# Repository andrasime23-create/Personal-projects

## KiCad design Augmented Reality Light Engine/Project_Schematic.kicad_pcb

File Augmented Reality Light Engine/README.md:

# Augmented Reality Light Engine

This project involves the complete design and development of an Augmented Reality (AR) Light Engine module. It showcases expertise in high-density electronics, bridging hardware architecture with advanced PCB manufacturing techniques. 

Core Architecture of the project implemented in KiCad: 

-**Powered by a DPLC2020 ASIC (ARM Cortex M3) and a DLPA2020 PMIC** to manage complex power rails.

-**Optical Engine**: Integrates a DLP2020 MEMS projector with OSRAM RGB LEDs to generate high-fidelity AR visuals.

-**Rigid-Flex Technology**: Designed on a 6-layer Rigid-Flex PCB to fit the ergonomic constraints of wearable smart glasses.

-**Signal & Power Integrity**: Implementation of 50Ω single-ended and 100Ω differential pairs for high-speed video data, alongside optimized switching loops for EMC compliance.

-**Thermal Engineering**: Utilizes Copper Inlays (copper coins) and calculated thermal via arrays to dissipate heat from high-power LEDs and the PMIC.

The system also provides manufacturing-ready files, including Extended Gerber, NC Drill, and Pick-and-Place data and detailed thermal resistance calculations and power integrity reports based on IPC-2152 standards, with the possibility of actually sending the prototype to the production line and developing a real functional project.

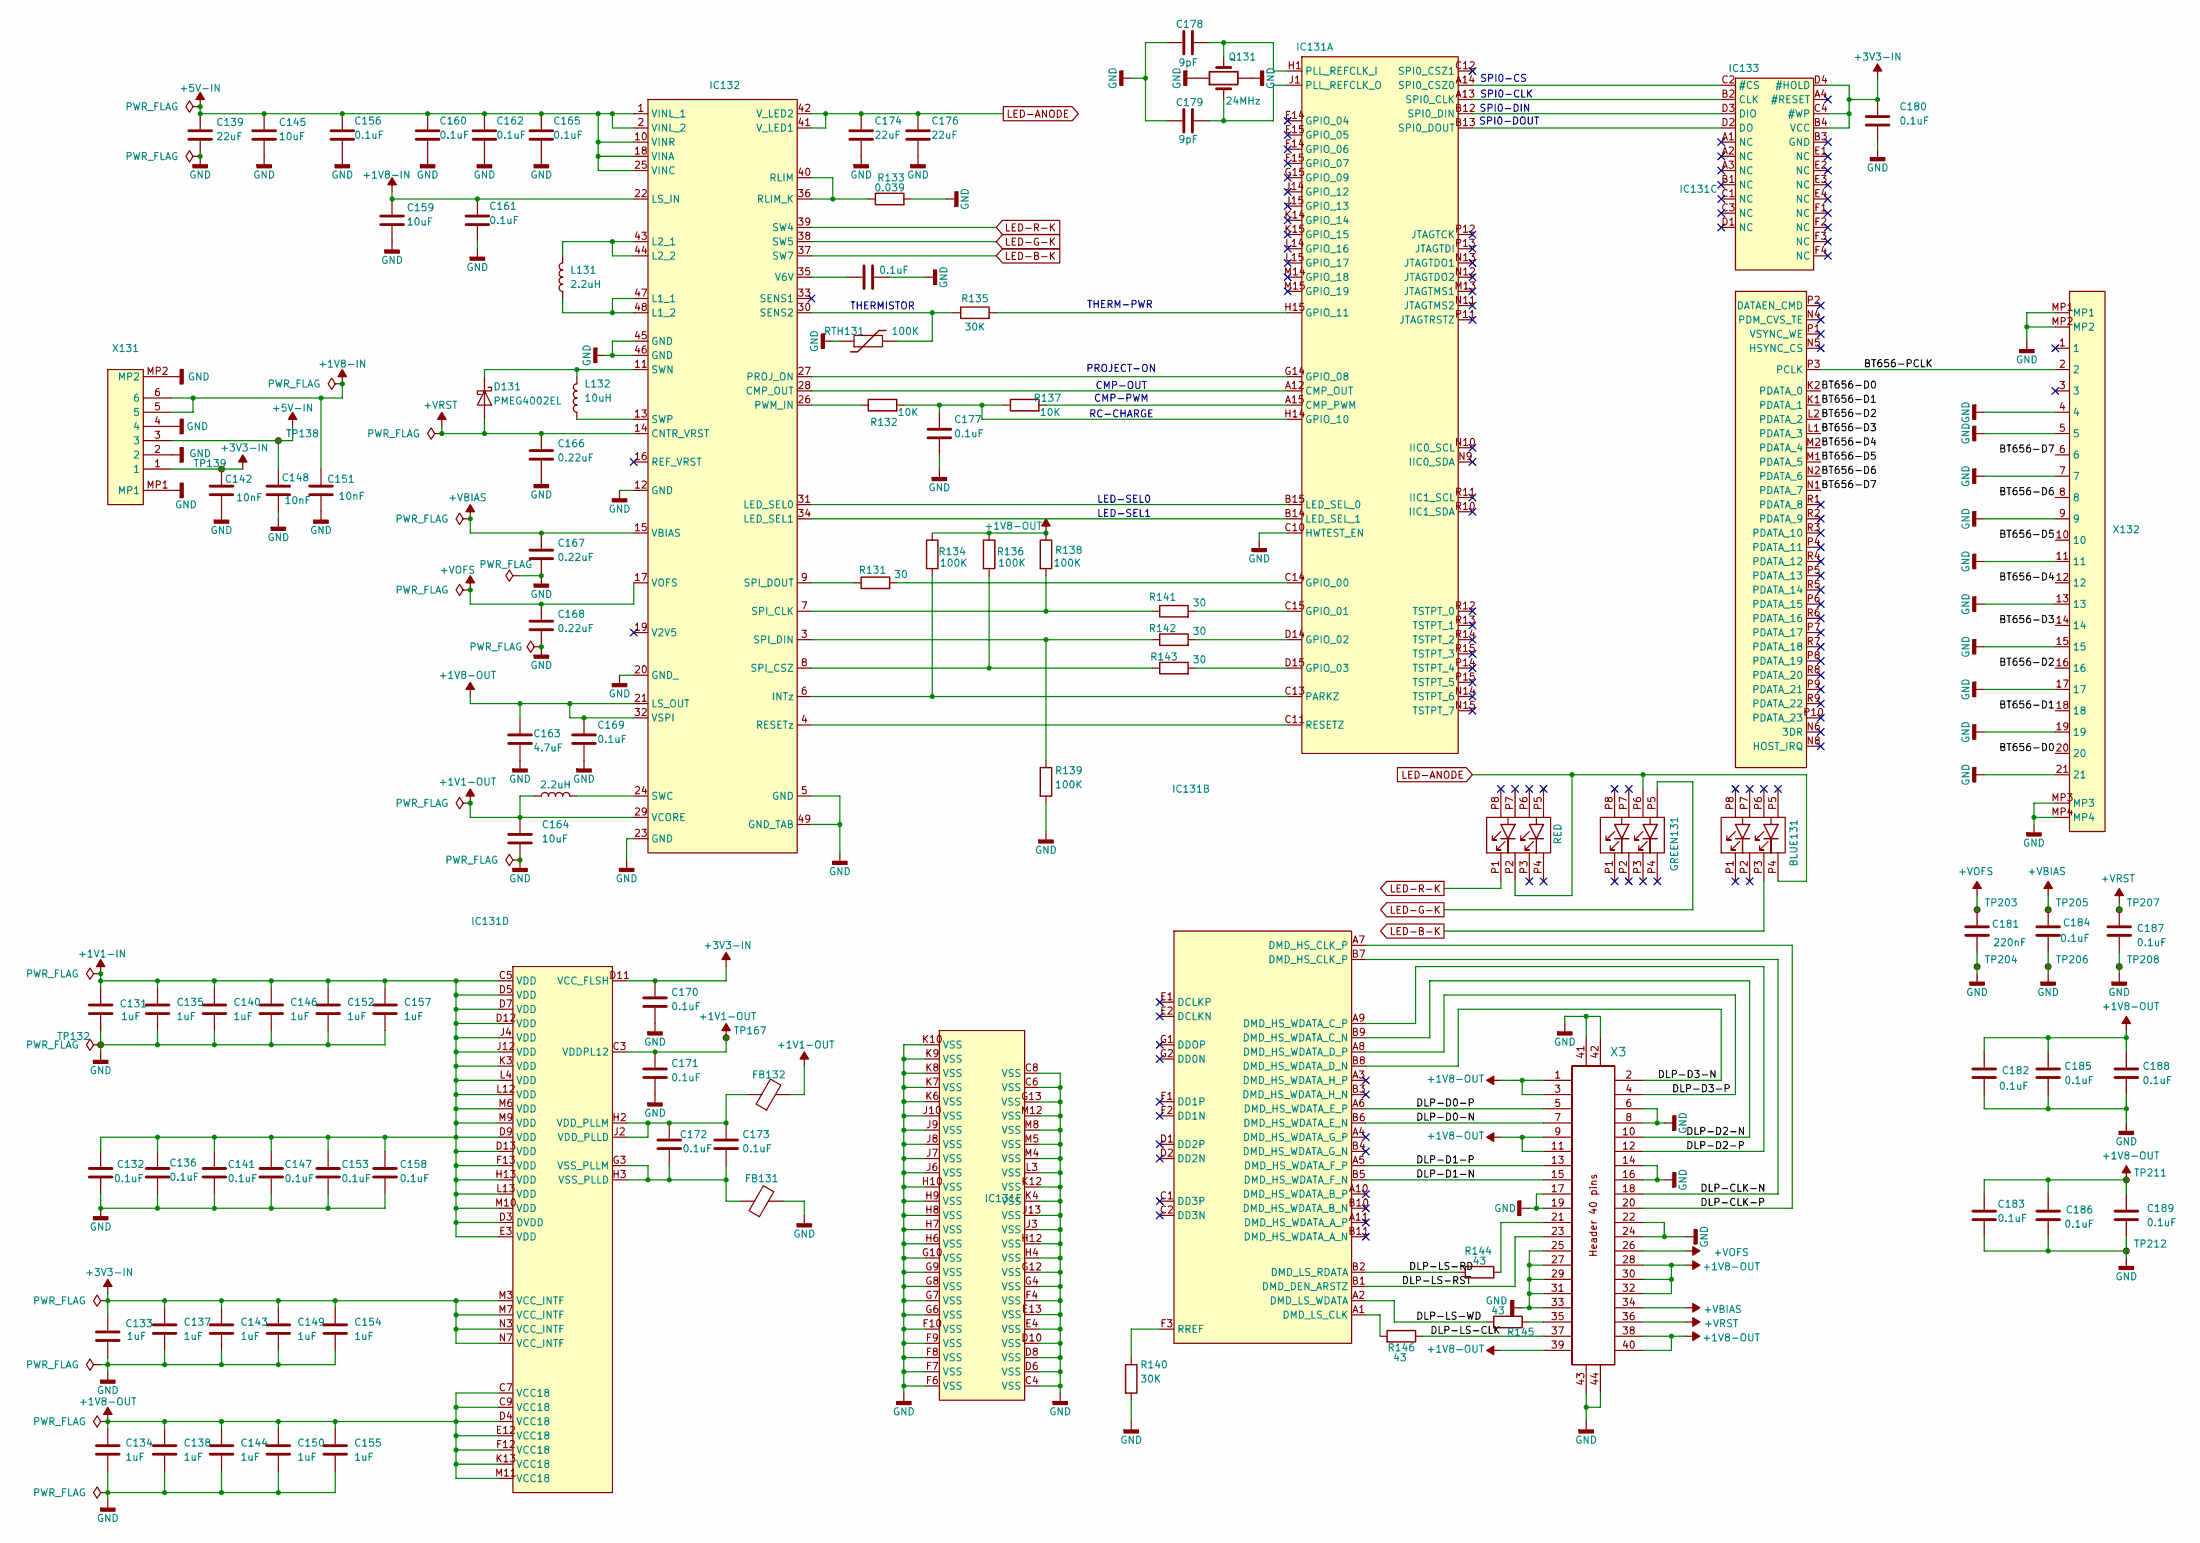
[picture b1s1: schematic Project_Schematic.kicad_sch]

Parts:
BLUE131: LE RTDUW S2WN_OSR
C131, C133, C134, C135, C137, C138, C140, C143, C144, C146, C149, C150, C152, C154, C155, C157: 1uF; C_0402_1005Metric
C132, C136, C141, C147, C153, C156, C158, C160, C161, C162, C165, C169, C170, C171, C172, C173, C175, C177, C180, C182, C183, C184, C185, C186, C187, C188, C189: 0.1uF; C_0402_1005Metric
C139, C174, C176: 22uF; C_0603_1608Metric
C142, C148, C151: 10nF; C_0402_1005Metric
C145, C159, C164: 10uF; C_0603_1608Metric
C163: 4.7uF; C_0603_1608Metric
C166, C167, C168: 0.22uF; C_0402_1005Metric
C178, C179: 9pF; C_0402_1005Metric
C181: 220nF; C_0603_1608Metric
D131: PMEG4002EL; D_SOD-882 (1)
FB131, FB132: FB_0402; L_0402_1005Metric
GREEN131: LE RTDUW S2WN_OSR
IC131: BGA-225_15x15_13.1x13.1mm
IC132: QFN-48_EP_6.8x6.8_Pitch0.4mm
IC133: BGA-24_4x6_6.0x8.0mm
J131: X3; AXT640124
L131: 2.2uH; L_Vishay_IHLP-1616
L132: 10uH; L_0805_2012Metric
LR131: 2.2uH; L_0603_1608Metric
Q131: 24MHz; Oscillator_SMD_Abracon_ASCO-4Pin_1.6x1.2mm
R131, R141, R142, R143: 30; R_0402_1005Metric
R132, R137: 10K; R_0402_1005Metric
R133: 0.039; R_0603_1608Metric
R134, R136, R138, R139: 100K; R_0402_1005Metric
R135, R140: 30K; R_0402_1005Metric
R144, R145, R146: 43; R_0402_1005Metric
RED131: RED; LE RTDUW S2WN_OSR
RTH131: 100K; R_0402_1005Metric
TP132, TP138, TP139, TP167, TP203, TP204, TP205, TP206, TP207, TP208, TP211, TP212: TestPoint_Small; TestPoint_Pad_D1.0mm
X131: CONN06_781715006_MOL
X132: FH6221S025SHW99

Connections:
+1V1-IN: C131.1, C132.1, C135.1, C136.1, C140.1, C141.1, C146.1, C147.1, C152.1, C153.1, C157.1, C158.1, IC131.C5 (VDD), IC131.D3 (DVDD), IC131.D5 (VDD), IC131.D7 (VDD), IC131.D9 (VDD), IC131.D12 (VDD), IC131.D13 (VDD), IC131.E3 (VDD), IC131.F13 (VDD), IC131.H13 (VDD), IC131.J4 (VDD), IC131.J12 (VDD), IC131.K3 (VDD), IC131.L4 (VDD), IC131.L12 (VDD), IC131.L13 (VDD), IC131.M6 (VDD), IC131.M9 (VDD), IC131.M10 (VDD)
+1V1-OUT: C164.1, C171.1, FB132.2, IC131.C3 (VDDPL12), IC132.29 (VCORE), LR131.1, TP167.1
+1V8-IN: C151.1, C159.1, C161.1, IC132.22 (LS_IN), X131.5, X131.6
+1V8-OUT: C134.1, C138.1, C144.1, C150.1, C155.1, C163.1, C169.1, C182.1, C183.1, C185.1, C186.1, C188.1, C189.1, IC131.C7 (VCC18), IC131.C9 (VCC18), IC131.D4 (VCC18), IC131.E12 (VCC18), IC131.F12 (VCC18), IC131.K13 (VCC18), IC131.M11 (VCC18), IC132.21 (LS_OUT), IC132.32 (VSPI), J131.1, J131.3, J131.9, J131.11, J131.28, J131.30, J131.32, J131.38, J131.39, J131.40, R134.1, R136.1, R138.1, TP211.1
+3V3-IN: C133.1, C137.1, C142.1, C143.1, C149.1, C154.1, C170.1, C180.1, IC131.D11 (VCC_FLSH), IC131.M3 (VCC_INTF), IC131.M7 (VCC_INTF), IC131.N3 (VCC_INTF), IC131.N7 (VCC_INTF), IC133.B4 (VCC), IC133.C4 (#WP), IC133.D4 (#HOLD), TP139.1, X131.1
+5V-IN: C139.1, C145.1, C148.1, C156.1, C160.1, C162.1, C165.1, IC132.1 (VINL_1), IC132.2 (VINL_2), IC132.10 (VINR), IC132.18 (VINA), IC132.25 (VINC), TP138.1, X131.3
+VBIAS: C167.1, C184.1, IC132.15 (VBIAS), J131.34, TP205.1
+VOFS: C168.1, C181.1, IC132.17 (VOFS), J131.26, TP203.1
+VRST: C166.1, C187.1, D131.2 (A), IC132.14 (CNTR_VRST), J131.36, TP207.1
/ BT656-D0: IC131.K2 (PDATA_0), X132.20
/ BT656-D1: IC131.K1 (PDATA_1), X132.18
/ BT656-D2: IC131.L2 (PDATA_2), X132.16
/ BT656-D3: IC131.L1 (PDATA_3), X132.14
/ BT656-D4: IC131.M2 (PDATA_4), X132.12
/ BT656-D5: IC131.M1 (PDATA_5), X132.10
/ BT656-D6: IC131.N2 (PDATA_6), X132.8
/ BT656-D7: IC131.N1 (PDATA_7), X132.6
/ BT656-PCLK: IC131.P3 (PCLK), X132.2
/ DLP-D2-N: IC131.B9 (DMD_HS_WDATA_C_N), J131.10
/ DLP-D2-P: IC131.A9 (DMD_HS_WDATA_C_P), J131.12
/DLP-CLK-N: IC131.B7 (DMD_HS_CLK_P), J131.18
/DLP-CLK-P: IC131.A7 (DMD_HS_CLK_P), J131.20
/DLP-D0-N: IC131.B6 (DMD_HS_WDATA_E_N), J131.7
/DLP-D0-P: IC131.A6 (DMD_HS_WDATA_E_P), J131.5
/DLP-D1-N: IC131.B5 (DMD_HS_WDATA_F_N), J131.15
/DLP-D1-P: IC131.A5 (DMD_HS_WDATA_F_P), J131.13
/DLP-D3-N: IC131.B8 (DMD_HS_WDATA_D_N), J131.2
/DLP-D3-P: IC131.A8 (DMD_HS_WDATA_D_P), J131.4
/DLP-LS-CLK: J131.37, R146.2
/DLP-LS-RD: IC131.B2 (DMD_LS_RDATA), R144.1
/DLP-LS-RST: IC131.B1 (DMD_DEN_ARSTZ), J131.23
/DLP-LS-WD: IC131.A2 (DMD_LS_WDATA), R145.1
GND: C131.2, C132.2, C133.2, C134.2, C135.2, C136.2, C137.2, C138.2, C139.2, C140.2, C141.2, C142.2, C143.2, C144.2, C145.2, C146.2, C147.2, C148.2, C149.2, C150.2, C151.2, C152.2, C153.2, C154.2, C155.2, C156.2, C157.2, C158.2, C159.2, C160.2, C161.2, C162.2, C163.2, C164.2, C165.2, C166.2, C167.2, C168.2, C169.2, C170.2, C171.2, C174.2, C175.2, C176.2, C177.2, C178.1, C179.1, C180.2, C181.2, C182.2, C183.2, C184.2, C185.2, C186.2, C187.2, C188.2, C189.2, FB131.2, IC131.C4 (VSS), IC131.C6 (VSS), IC131.C8 (VSS), IC131.C10 (HWTEST_EN), IC131.D6 (VSS), IC131.D8 (VSS), IC131.D10 (VSS), IC131.E4 (VSS), IC131.E13 (VSS), IC131.F4 (VSS), IC131.F6 (VSS), IC131.F7 (VSS), IC131.F8 (VSS), IC131.F9 (VSS), IC131.F10 (VSS), IC131.G4 (VSS), IC131.G6 (VSS), IC131.G7 (VSS), IC131.G8 (VSS), IC131.G9 (VSS), IC131.G10 (VSS), IC131.G12 (VSS), IC131.G13 (VSS), IC131.H4 (VSS), IC131.H6 (VSS), IC131.H7 (VSS), IC131.H8 (VSS), IC131.H9 (VSS), IC131.H10 (VSS), IC131.H12 (VSS), IC131.J3 (VSS), IC131.J6 (VSS), IC131.J7 (VSS), IC131.J8 (VSS), IC131.J9 (VSS), IC131.J10 (VSS), IC131.J13 (VSS), IC131.K4 (VSS), IC131.K6 (VSS), IC131.K7 (VSS), IC131.K8 (VSS), IC131.K9 (VSS), IC131.K10 (VSS), IC131.K12 (VSS), IC131.L3 (VSS), IC131.M4 (VSS), IC131.M5 (VSS), IC131.M8 (VSS), IC131.M12 (VSS), IC132.5 (GND), IC132.12 (GND), IC132.20 (GND_), IC132.23 (GND), IC132.45 (GND), IC132.46 (GND), IC132.49 (GND_TAB), J131.6, J131.8, J131.14, J131.16, J131.17, J131.19, J131.22, J131.24, J131.25, J131.27, J131.29, J131.31, J131.33, J131.41, J131.42, J131.43, J131.44, Q131.3, Q131.4, R133.2, R139.2, R140.2, RTH131.1, TP132.1, TP204.1, TP206.1, TP208.1, TP212.1, X131.2, X131.4, X131.MP1, X131.MP2, X132.4, X132.5, X132.7, X132.9, X132.11, X132.13, X132.15, X132.17, X132.19, X132.21, X132.MP1, X132.MP2, X132.MP3, X132.MP4
LED-ANODE: BLUE131.P4, C174.1, C176.1, GREEN131.P6, IC132.41 (V_LED1), IC132.42 (V_LED2), RED131.P2
LED-B-K: BLUE131.P3, IC132.37 (SW7)
LED-G-K: GREEN131.P5, IC132.38 (SW5)
LED-R-K: IC132.39 (SW4), RED131.P1
unnamed: D131.1 (K), IC132.11 (SWN), L132.2
unnamed: IC131.A12 (CMP_OUT), IC132.28 (CMP_OUT)
unnamed: IC131.A15 (CMP_PWM), R137.2
unnamed: IC131.C14 (GPIO_00), R131.2
unnamed: IC131.C15 (GPIO_01), R141.2
unnamed: IC131.D14 (GPIO_02), R142.2
unnamed: IC131.D15 (GPIO_03), R143.2
unnamed: IC131.G14 (GPIO_08), IC132.27 (PROJ_ON)
unnamed: C177.1, IC131.H14 (GPIO_10), R132.2, R137.1
unnamed: IC131.H15 (GPIO_11), R135.2
unnamed: IC131.B15 (LED_SEL_0), IC132.31 (LED_SEL0)
unnamed: IC131.B14 (LED_SEL_1), IC132.34 (LED_SEL1)
unnamed: IC131.C13 (PARKZ), IC132.6 (INTz), R134.2
unnamed: C178.2, IC131.H1 (PLL_REFCLK_I), Q131.2
unnamed: C179.2, IC131.J1 (PLL_REFCLK_O), Q131.1
unnamed: IC131.C11 (RESETZ), IC132.4 (RESETz)
unnamed: IC131.A13 (SPI0_CLK), IC133.B2 (CLK)
unnamed: IC131.A14 (SPI0_CSZ0), IC133.C2 (#CS)
unnamed: IC131.B12 (SPI0_DIN), IC133.D3 (DIO)
unnamed: IC131.B13 (SPI0_DOUT), IC133.D2 (DO)
unnamed: IC131.A1 (DMD_LS_CLK), R146.1
unnamed: IC131.F3 (RREF), R140.1
unnamed: C172.1, C173.1, FB132.1, IC131.H2 (VDD_PLLM), IC131.J2 (VDD_PLLD)
unnamed: C172.2, C173.2, FB131.1, IC131.G3 (VSS_PLLM), IC131.H3 (VSS_PLLD)
unnamed: IC132.47 (L1_1), IC132.48 (L1_2), L131.1
unnamed: IC132.43 (L2_1), IC132.44 (L2_2), L131.2
unnamed: IC132.26 (PWM_IN), R132.1
unnamed: IC132.36 (RLIM_K), IC132.40 (RLIM), R133.1
unnamed: IC132.30 (SENS2), R135.1, RTH131.2
unnamed: IC132.7 (SPI_CLK), R138.2, R141.1
unnamed: IC132.8 (SPI_CSZ), R136.2, R143.1
unnamed: IC132.3 (SPI_DIN), R139.1, R142.1
unnamed: IC132.9 (SPI_DOUT), R131.1
unnamed: IC132.24 (SWC), LR131.2
unnamed: IC132.13 (SWP), L132.1
unnamed: C175.1, IC132.35 (V6V)
unnamed: J131.21, R144.2
unnamed: J131.35, R145.2

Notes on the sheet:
SPI0-DOUT
THERMISTOR
CMP-PWM
SPI0-CS
PROJECT-ON
RC-CHARGE
CMP-OUT
SPI0-DIN
SPI0-CLK
LED-SEL1
LED-SEL0
THERM-PWR

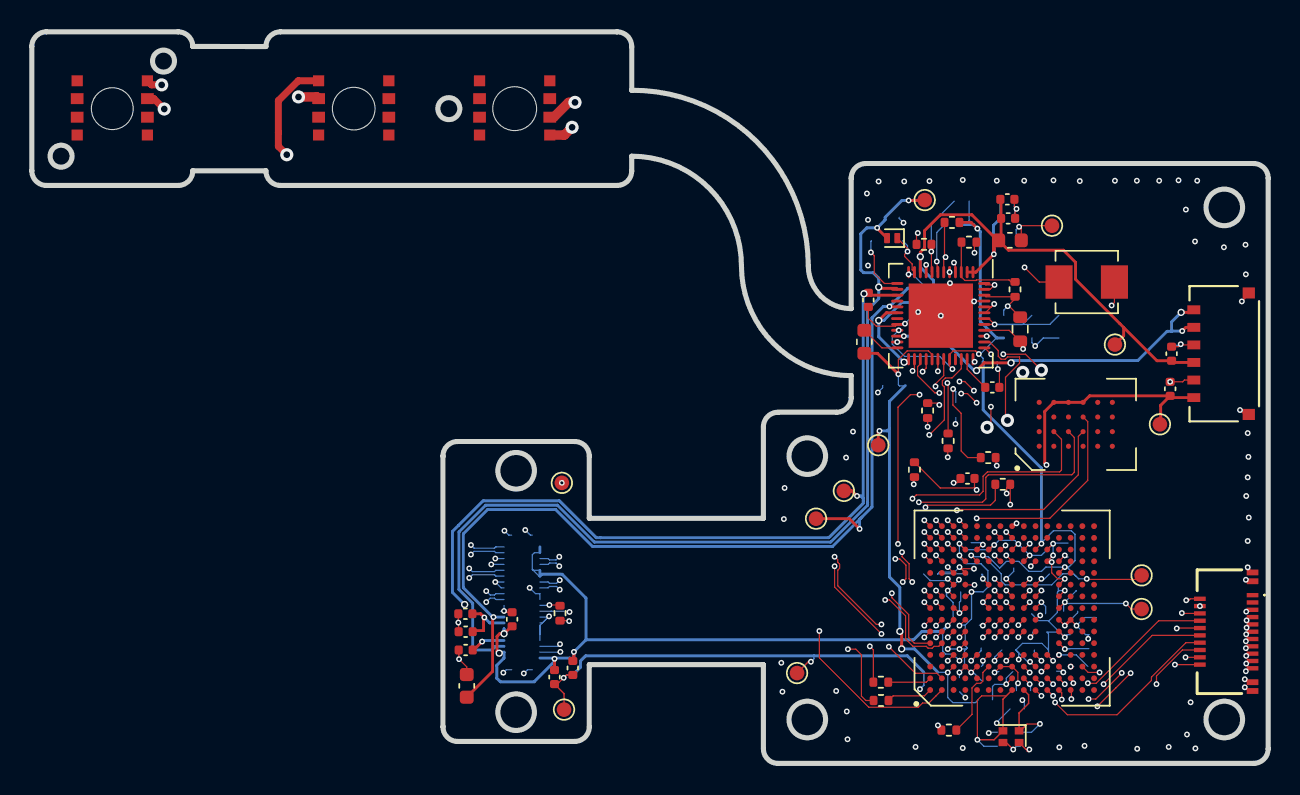
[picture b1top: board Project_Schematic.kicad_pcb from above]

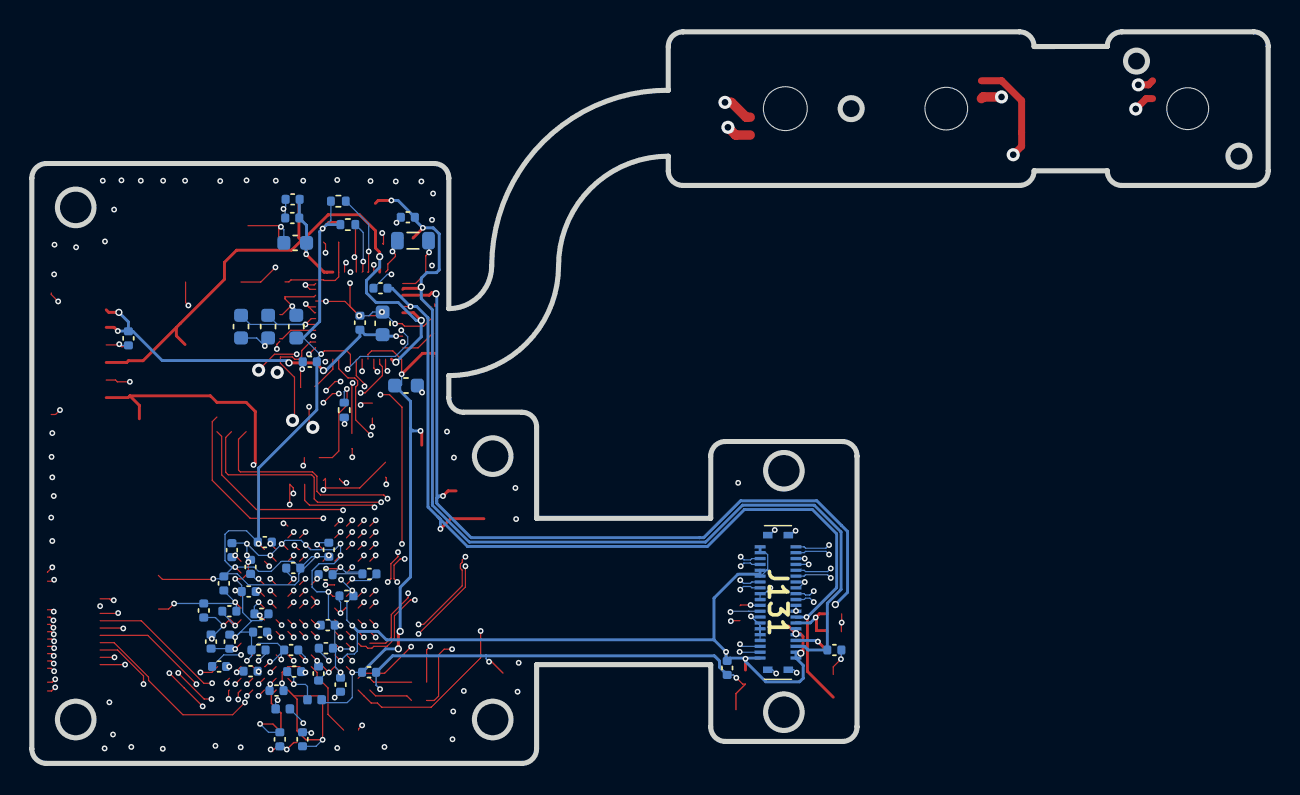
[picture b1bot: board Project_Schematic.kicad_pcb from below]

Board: 6 copper layers, 84.5 x 50.0 mm, 104 parts (51 on the bottom side), 75 nets.

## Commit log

2026-05-01 Create README.md for Power-sources folder
2026-05-01 Added afferent folders to this project
2026-05-01 Revise README with project goals and steps
    Updated project aims and steps for power source design.
2026-05-01 Create Digital Image Processing
2026-05-01 Create initial README file for digital-image-processing folder
2026-05-01 Create README.md for Augmented Reality Light Engine
2026-05-01 Created new directory for PCB Design
2026-05-01 Revise README for Augmented Reality Light Engine project
    Updated README to provide detailed project overview and technical specifications.
2026-05-01 Created DC-DC Power Source Design folder
2026-05-01 Create new folders
2026-05-01 Add README for Modular Analog Signal Processing Pipeline
    Added detailed project description and system architecture for the modular analog signal processing pipeline.
2026-05-01 Created readme
2026-05-01 file created
2026-05-01 new folders
